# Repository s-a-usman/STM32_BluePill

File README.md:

# STM32_BluePill
This GitHub repository contains an implementation and demonstration of the STM32 design tutorial using KiCad 6. It includes schematic designs, PCB layouts, and related project files created with KiCad 6 for an STM32 microcontroller-based circuit.

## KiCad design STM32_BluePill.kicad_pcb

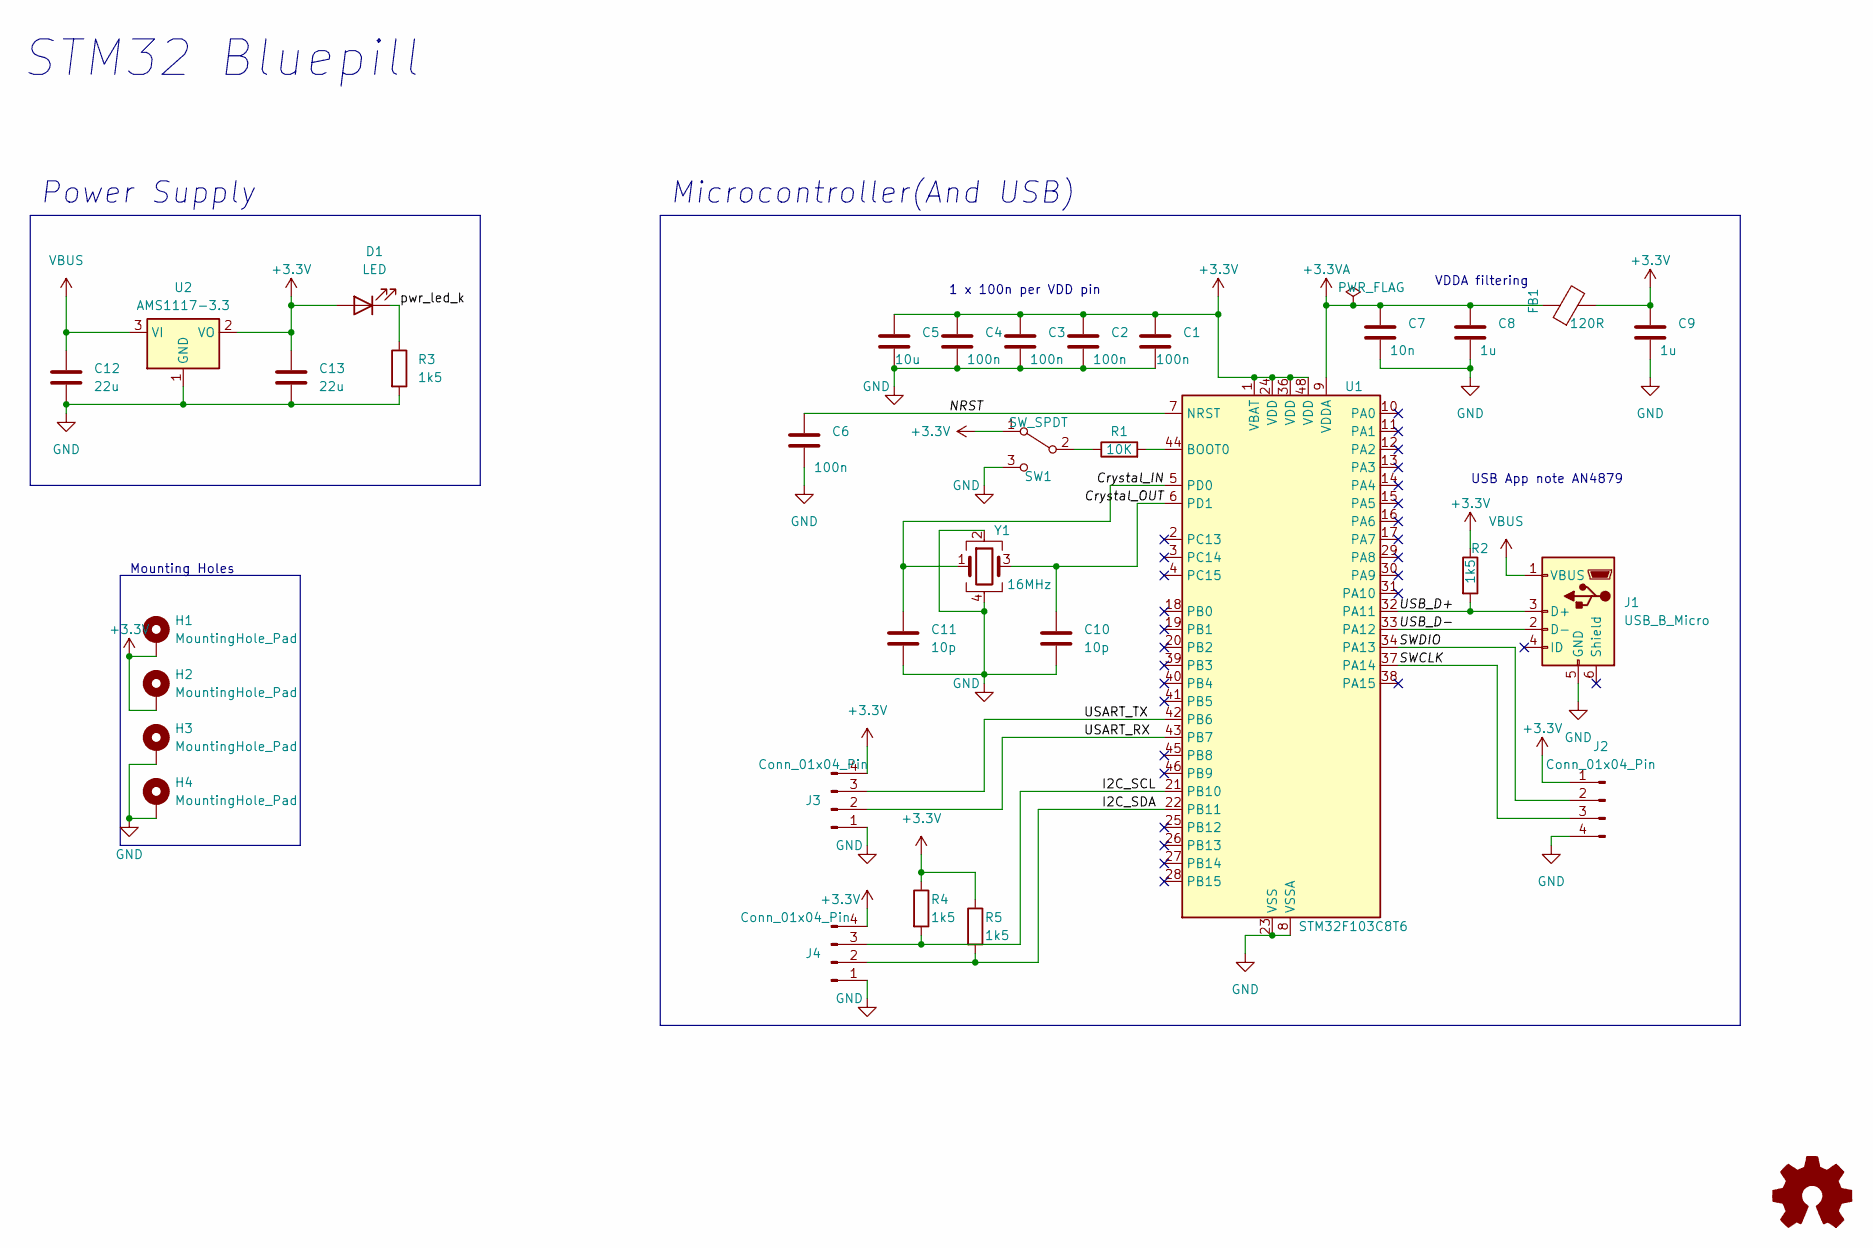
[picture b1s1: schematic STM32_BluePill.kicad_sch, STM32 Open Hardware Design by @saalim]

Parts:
C1, C2, C3, C4, C6: 100n; C_0402_1005Metric
C5: 10u; C_0603_1608Metric
C7: 10n; C_0402_1005Metric
C8, C9: 1u; C_0603_1608Metric
C10, C11: 10p; C_0402_1005Metric
C12, C13: 22u; C_0805_2012Metric
D1: LED; LED_0603_1608Metric
FB1: 120R; L_0805_2012Metric
H1, H2, H3, H4: MountingHole_Pad; MountingHole_2.2mm_M2_ISO7380_Pad
J1: USB_B_Micro; USB_Micro-B_Molex_47346-0001
J2, J3, J4: Conn_01x04_Pin; PinHeader_1x04_P2.54mm_Vertical
R1: 10K; R_0603_1608Metric
R2, R3, R4, R5: 1k5; R_0402_1005Metric
SW1: SW_SPDT; SW_CuK_JS202011AQN_DPDT_Angled
U1: STM32F103C8T6; LQFP-48_7x7mm_P0.5mm
U2: AMS1117-3.3; SOT-223-3_TabPin2
Y1: 16MHz; Crystal_SMD_3225-4Pin_3.2x2.5mm

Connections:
+3.3V: C1.1, C2.1, C3.1, C4.1, C5.1, C9.1, C13.1, D1.2 (A), FB1.2, H1.1, H2.1, J2.1, J3.4, J4.4, R2.1, R4.1, R5.1, SW1.1 (A), U1.1 (VBAT), U1.24 (VDD), U1.36 (VDD), U1.48 (VDD), U2.2 (VO)
+3.3VA: C7.1, C8.1, FB1.1, U1.9 (VDDA)
/Crystal_IN: C11.1, U1.5 (PD0), Y1.1
/Crystal_OUT: C10.1, U1.6 (PD1), Y1.3
/I2C_SCL: J4.3, R4.2, U1.21 (PB10)
/I2C_SDA: J4.2, R5.2, U1.22 (PB11)
/NRST: C6.1, U1.7 (NRST)
/SWCLK: J2.3, U1.37 (PA14)
/SWDIO: J2.2, U1.34 (PA13)
/USART_RX: J3.2, U1.43 (PB7)
/USART_TX: J3.3, U1.42 (PB6)
/USB_D+: J1.3 (D+), R2.2, U1.32 (PA11)
/USB_D-: J1.2 (D-), U1.33 (PA12)
/pwr_led_k: D1.1 (K), R3.1
GND: C1.2, C2.2, C3.2, C4.2, C5.2, C6.2, C7.2, C8.2, C9.2, C10.2, C11.2, C12.2, C13.2, H3.1, H4.1, J1.5 (GND), J2.4, J3.1, J4.1, R3.2, SW1.3 (C), U1.8 (VSSA), U1.23 (VSS), U1.35 (VSS), U1.47 (VSS), U2.1 (GND), Y1.2, Y1.4
unnamed: R1.1, SW1.2 (B)
unnamed: R1.2, U1.44 (BOOT0)
VBUS: C12.1, J1.1 (VBUS), U2.3 (VI)

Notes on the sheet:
1 x 100n per VDD pin
VDDA filtering
Mounting Holes
USB App note AN4879
STM32 Bluepill
Power Supply
Microcontroller(And USB)

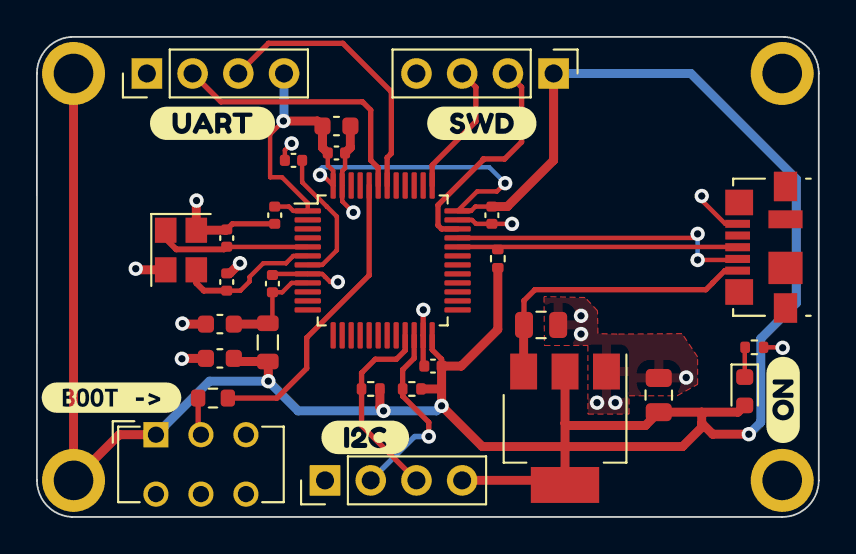
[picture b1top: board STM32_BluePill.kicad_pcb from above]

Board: 2 copper layers, 43.4 x 26.7 mm, 37 parts (0 on the bottom side), 18 nets.

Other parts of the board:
kibuzzard-653AD9F9: G***; kibuzzard-653AD9F9
kibuzzard-653AD99E: G***; kibuzzard-653AD99E
kibuzzard-653AD947: G***; kibuzzard-653AD947
kibuzzard-653AD972: G***; kibuzzard-653AD972
kibuzzard-653ADAE2: G***; kibuzzard-653ADAE2

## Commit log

2023-12-20 Update README.md
    More info
2023-12-20 Add KiCad files
2023-12-20 Update README.md
    Add sample image
